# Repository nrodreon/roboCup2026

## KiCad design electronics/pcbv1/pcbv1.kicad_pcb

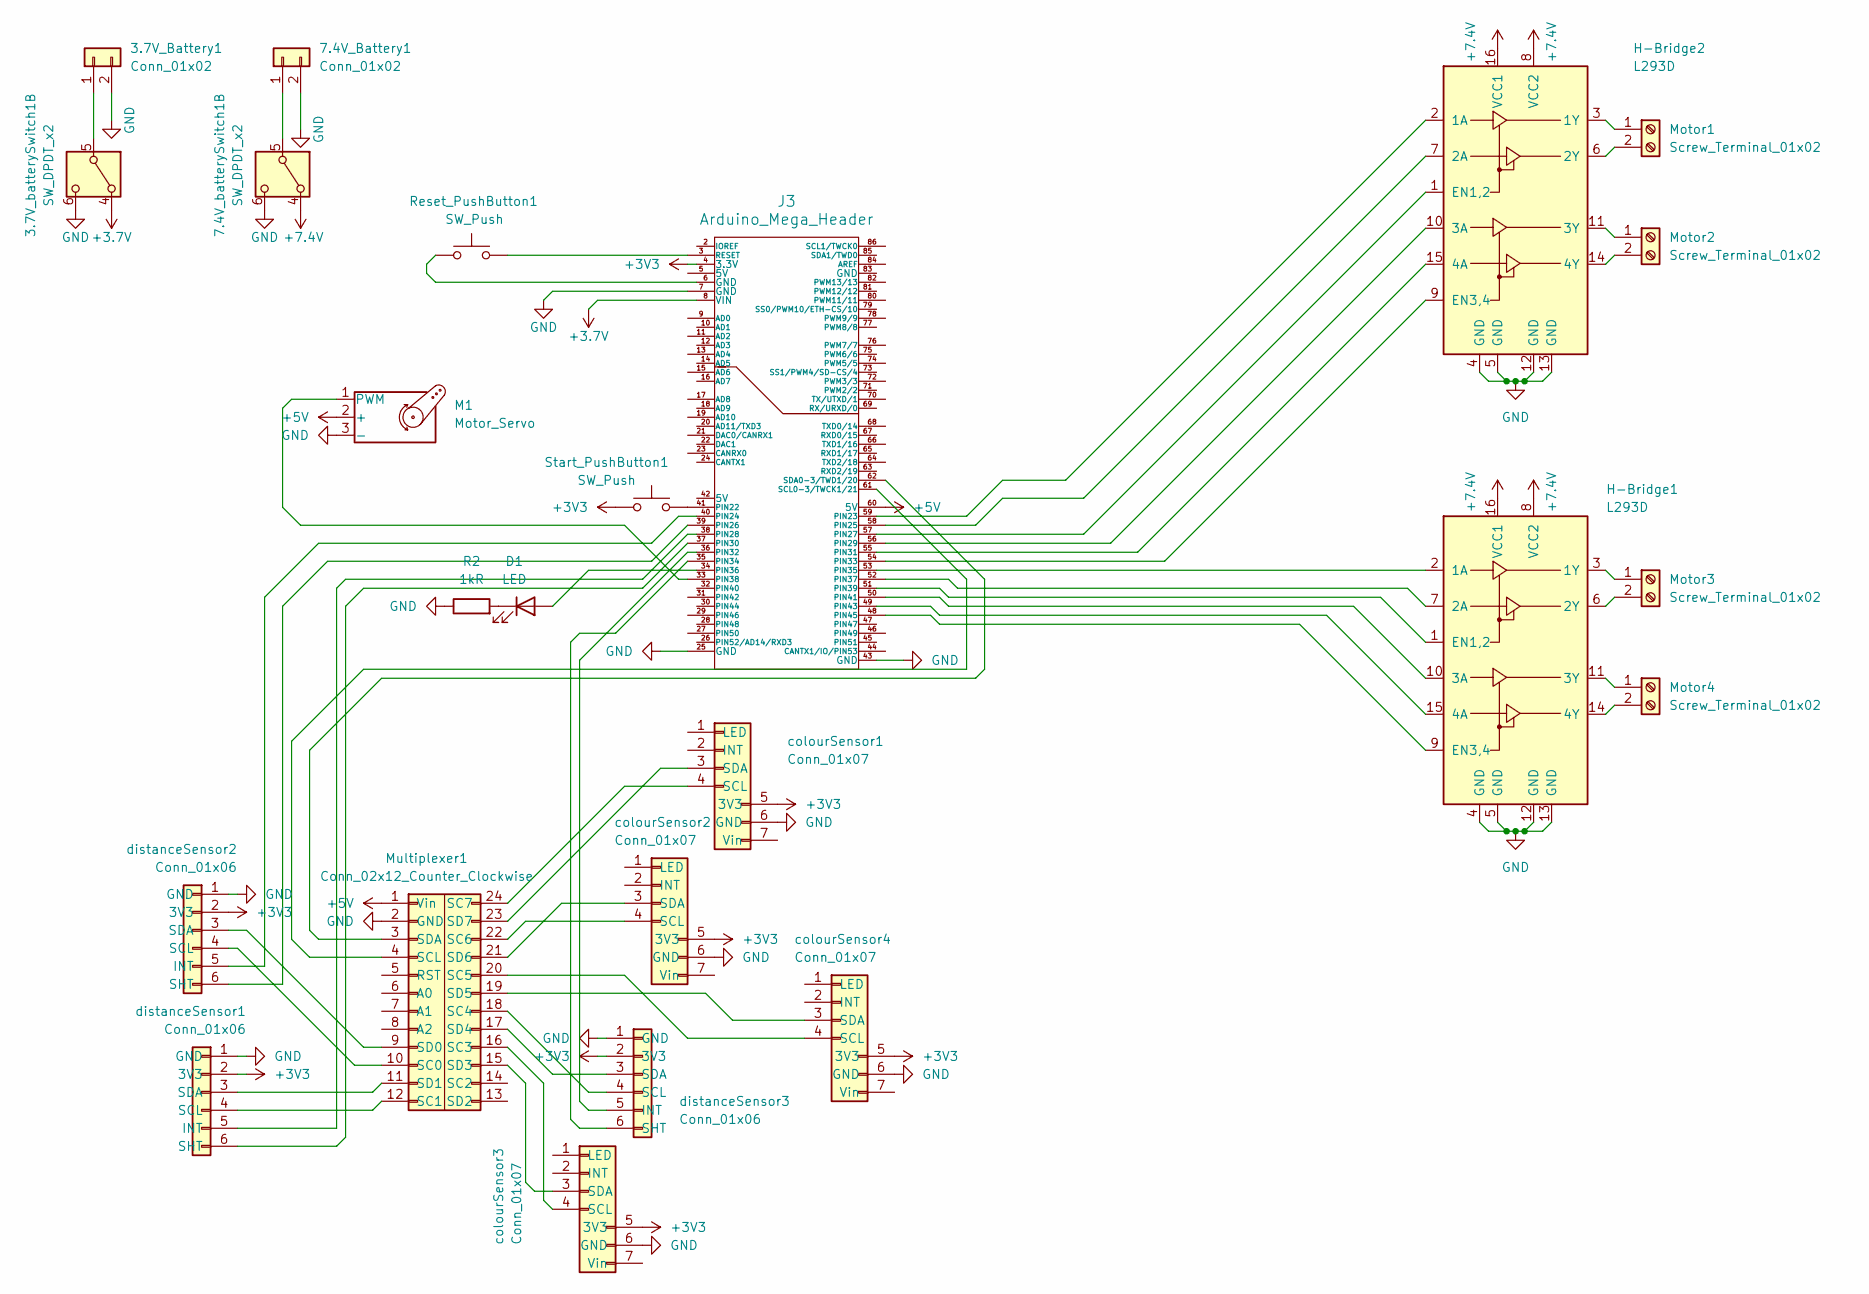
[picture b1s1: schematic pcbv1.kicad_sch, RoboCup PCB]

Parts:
3.7V_Battery1: Conn_01x02; PinSocket_1x02_P2.54mm_Vertical
3.7V_batterySwitch1, 7.4V_batterySwitch1: SW_DPDT_x2; SW_Slide_SPDT_Straight_CK_OS102011MS2Q
7.4V_Battery1: Conn_01x02; TerminalBlock_Xinya_XY308-2.54-2P_1x02_P2.54mm_Horizontal
D1: LED; LED_D5.0mm
H-Bridge1, H-Bridge2: L293D; DIP-16_W7.62mm
J3: Arduino_Mega_Header; Clone_Mega2560_Pro_Socket1
M1: Motor_Servo; PinSocket_1x03_P2.54mm_Vertical
Motor1, Motor2, Motor3, Motor4: Screw_Terminal_01x02; TerminalBlock_Xinya_XY308-2.54-2P_1x02_P2.54mm_Horizontal
Multiplexer1: Conn_02x12_Counter_Clockwise; PinSocket_2x12_P2.54mm_Vertical
R2: 1kR; R_Axial_DIN0207_L6.3mm_D2.5mm_P7.62mm_Horizontal
Reset_PushButton1: SW_Push; SW_TH_Tactile_Omron_B3F-100x
Start_PushButton1: SW_Push; SW_TH_Tactile_Omron_B3F-100x
colourSensor1, colourSensor2, colourSensor3, colourSensor4: Conn_01x07; PinSocket_1x07_P2.54mm_Vertical
distanceSensor1, distanceSensor2, distanceSensor3: Conn_01x06; PinSocket_1x06_P2.54mm_Vertical

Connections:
+3.7V: 3.7V_batterySwitch1.4 (A), J3.8 (VIN)
+3V3: J3.4 (3.3V), Start_PushButton1.1, colourSensor1.5 (3V3), colourSensor2.5 (3V3), colourSensor3.5 (3V3), colourSensor4.5 (3V3), distanceSensor1.2 (3V3), distanceSensor2.2 (3V3), distanceSensor3.2 (3V3)
+5V: J3.60 (5V), M1.2 (+), Multiplexer1.1 (Vin)
+7.4V: 7.4V_batterySwitch1.4 (A), H-Bridge1.8 (VCC2), H-Bridge1.16 (VCC1), H-Bridge2.8 (VCC2), H-Bridge2.16 (VCC1)
GND: 3.7V_Battery1.2, 3.7V_batterySwitch1.6 (C), 7.4V_Battery1.2, 7.4V_batterySwitch1.6 (C), H-Bridge1.4 (GND), H-Bridge1.5 (GND), H-Bridge1.12 (GND), H-Bridge1.13 (GND), H-Bridge2.4 (GND), H-Bridge2.5 (GND), H-Bridge2.12 (GND), H-Bridge2.13 (GND), J3.7 (GND), J3.25 (GND), J3.43 (GND), M1.3 (-), Multiplexer1.2 (GND), R2.1, colourSensor1.6 (GND), colourSensor2.6 (GND), colourSensor3.6 (GND), colourSensor4.6 (GND), distanceSensor1.1 (GND), distanceSensor2.1 (GND), distanceSensor3.1 (GND)
unnamed: 3.7V_Battery1.1, 3.7V_batterySwitch1.5 (B)
unnamed: 7.4V_Battery1.1, 7.4V_batterySwitch1.5 (B)
unnamed: D1.2 (A), J3.34 (PIN36)
unnamed: D1.1 (K), R2.2
unnamed: H-Bridge1.2 (1A), J3.53 (PIN35)
unnamed: H-Bridge1.3 (1Y), Motor3.1
unnamed: H-Bridge1.7 (2A), J3.52 (PIN37)
unnamed: H-Bridge1.6 (2Y), Motor3.2
unnamed: H-Bridge1.10 (3A), J3.50 (PIN41)
unnamed: H-Bridge1.11 (3Y), Motor4.1
unnamed: H-Bridge1.15 (4A), J3.49 (PIN43)
unnamed: H-Bridge1.14 (4Y), Motor4.2
unnamed: H-Bridge1.1 (EN1,2), J3.51 (PIN39)
unnamed: H-Bridge1.9 (EN3,4), J3.48 (PIN45)
unnamed: H-Bridge2.2 (1A), J3.59 (PIN23)
unnamed: H-Bridge2.3 (1Y), Motor1.1
unnamed: H-Bridge2.7 (2A), J3.58 (PIN25)
unnamed: H-Bridge2.6 (2Y), Motor1.2
unnamed: H-Bridge2.10 (3A), J3.56 (PIN29)
unnamed: H-Bridge2.11 (3Y), Motor2.1
unnamed: H-Bridge2.15 (4A), J3.55 (PIN31)
unnamed: H-Bridge2.14 (4Y), Motor2.2
unnamed: H-Bridge2.1 (EN1,2), J3.57 (PIN27)
unnamed: H-Bridge2.9 (EN3,4), J3.54 (PIN33)
unnamed: J3.6 (GND), Reset_PushButton1.1
unnamed: J3.41 (PIN22), Start_PushButton1.2
unnamed: J3.40 (PIN24), distanceSensor2.5 (INT)
unnamed: J3.39 (PIN26), distanceSensor2.6 (SHT)
unnamed: J3.38 (PIN28), distanceSensor1.5 (INT)
unnamed: J3.37 (PIN30), distanceSensor1.6 (SHT)
unnamed: J3.36 (PIN32), distanceSensor3.5 (INT)
unnamed: J3.35 (PIN34), distanceSensor3.6 (SHT)
unnamed: J3.33 (PIN38), M1.1 (PWM)
unnamed: J3.3 (RESET), Reset_PushButton1.2
unnamed: J3.61 (SCL0-3/TWCK1/21), Multiplexer1.4 (SCL)
unnamed: J3.62 (SDA0-3/TWD1/20), Multiplexer1.3 (SDA)
unnamed: Multiplexer1.10 (SC0), distanceSensor2.4 (SCL)
unnamed: Multiplexer1.12 (SC1), distanceSensor1.4 (SCL)
unnamed: Multiplexer1.16 (SC3), colourSensor3.4 (SCL)
unnamed: Multiplexer1.18 (SC4), distanceSensor3.4 (SCL)
unnamed: Multiplexer1.20 (SC5), colourSensor4.4 (SCL)
unnamed: Multiplexer1.22 (SC6), colourSensor2.4 (SCL)
unnamed: Multiplexer1.24 (SC7), colourSensor1.4 (SCL)
unnamed: Multiplexer1.9 (SD0), distanceSensor2.3 (SDA)
unnamed: Multiplexer1.11 (SD1), distanceSensor1.3 (SDA)
unnamed: Multiplexer1.15 (SD3), colourSensor3.3 (SDA)
unnamed: Multiplexer1.17 (SD4), distanceSensor3.3 (SDA)
unnamed: Multiplexer1.19 (SD5), colourSensor4.3 (SDA)
unnamed: Multiplexer1.21 (SD6), colourSensor2.3 (SDA)
unnamed: Multiplexer1.23 (SD7), colourSensor1.3 (SDA)

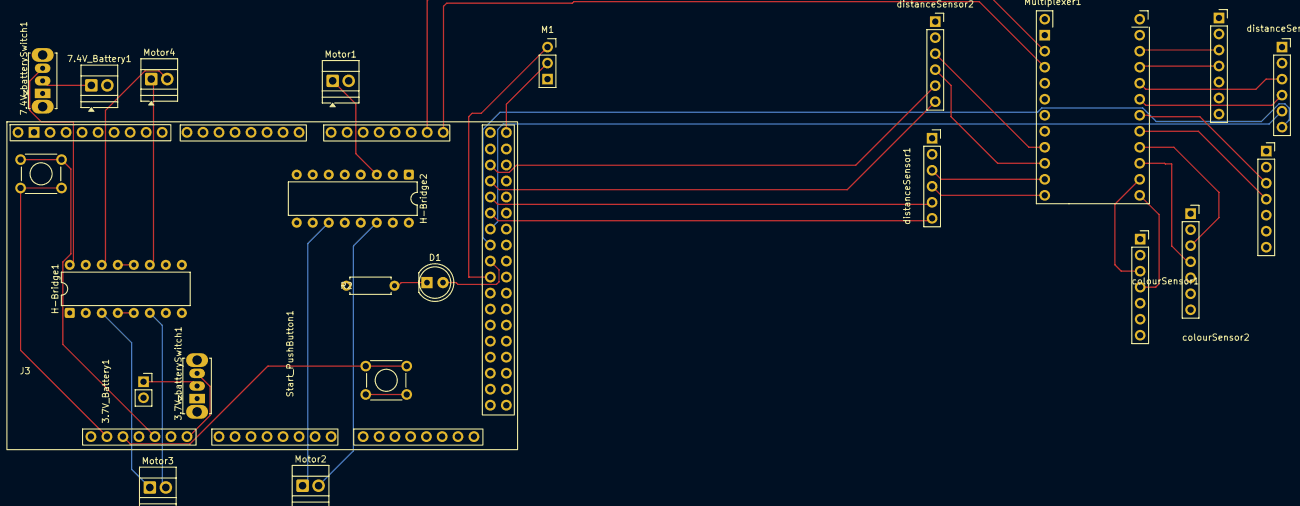
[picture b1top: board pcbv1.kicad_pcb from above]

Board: 4 copper layers, 24 parts (0 on the bottom side), 55 nets.
